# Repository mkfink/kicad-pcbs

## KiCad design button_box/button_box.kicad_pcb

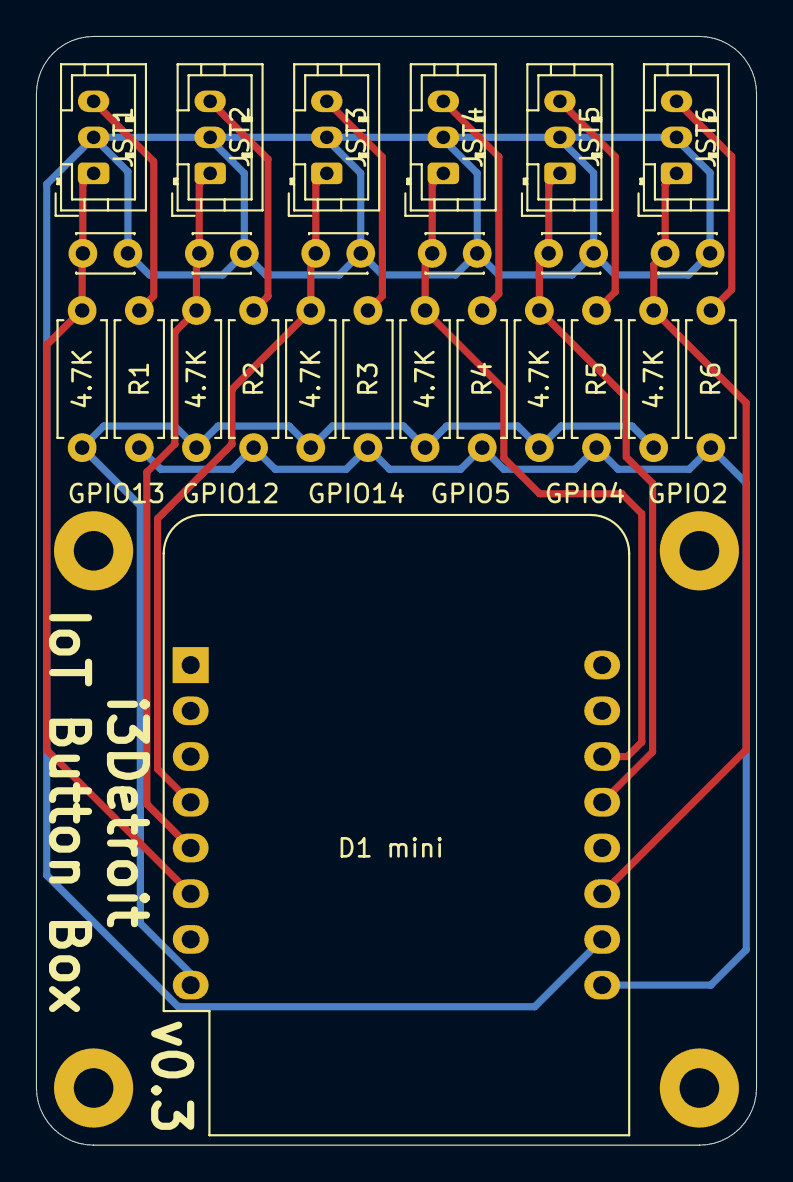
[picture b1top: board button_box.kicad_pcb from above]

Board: 2 copper layers, 40.0 x 61.6 mm, 29 parts (0 on the bottom side), 15 nets.

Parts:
4.7K, 4.7K#2, 4.7K#3, 4.7K#4, 4.7K#5, 4.7K#6: 4.7K; R_Axial_DIN0207_L6.3mm_D2.5mm_P7.62mm_Horizontal
C1, C2, C3, C4, C5, C6: 30 pF; C_Disc_D3.0mm_W2.0mm_P2.50mm
JST1, JST2, JST3, JST4, JST5, JST6: Conn_01x03_Male; JST_PH_B3B-PH-K_1x03_P2.00mm_Vertical
R1, R2, R3, R4, R5, R6: R; R_Axial_DIN0207_L6.3mm_D2.5mm_P7.62mm_Horizontal
U1: WeMos_D1_mini; WEMOS_D1_mini_light
hole: MountingHole_2.2mm_M2_Pad
hole#2, hole#3, hole#4: MountingHole_2.2mm_M2_Pad

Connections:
unnamed: 4.7K.1, C1.1, JST1.1, U1.6
unnamed: C1.2, C2.2, C3.2, C4.2, C5.2, C6.2, JST1.2, JST2.2, JST3.2, JST4.2, JST5.2, JST6.2, U1.10
unnamed: 4.7K#2.1, C2.1, JST2.1, U1.5
unnamed: 4.7K#3.1, C3.1, JST3.1, U1.4
unnamed: 4.7K#4.1, C4.1, JST4.1, U1.14
unnamed: 4.7K#5.1, C5.1, JST5.1, U1.13
unnamed: 4.7K#6.1, C6.1, JST6.1, U1.11
unnamed: JST6.3, R6.2
unnamed: JST5.3, R5.2
unnamed: JST4.3, R4.2
unnamed: JST3.3, R3.2
unnamed: JST2.3, R2.2
unnamed: JST1.3, R1.2
unnamed: R1.1, R2.1, R3.1, R4.1, R5.1, R6.1, U1.9
unnamed: 4.7K.2, 4.7K#2.2, 4.7K#3.2, 4.7K#4.2, 4.7K#5.2, 4.7K#6.2, U1.8

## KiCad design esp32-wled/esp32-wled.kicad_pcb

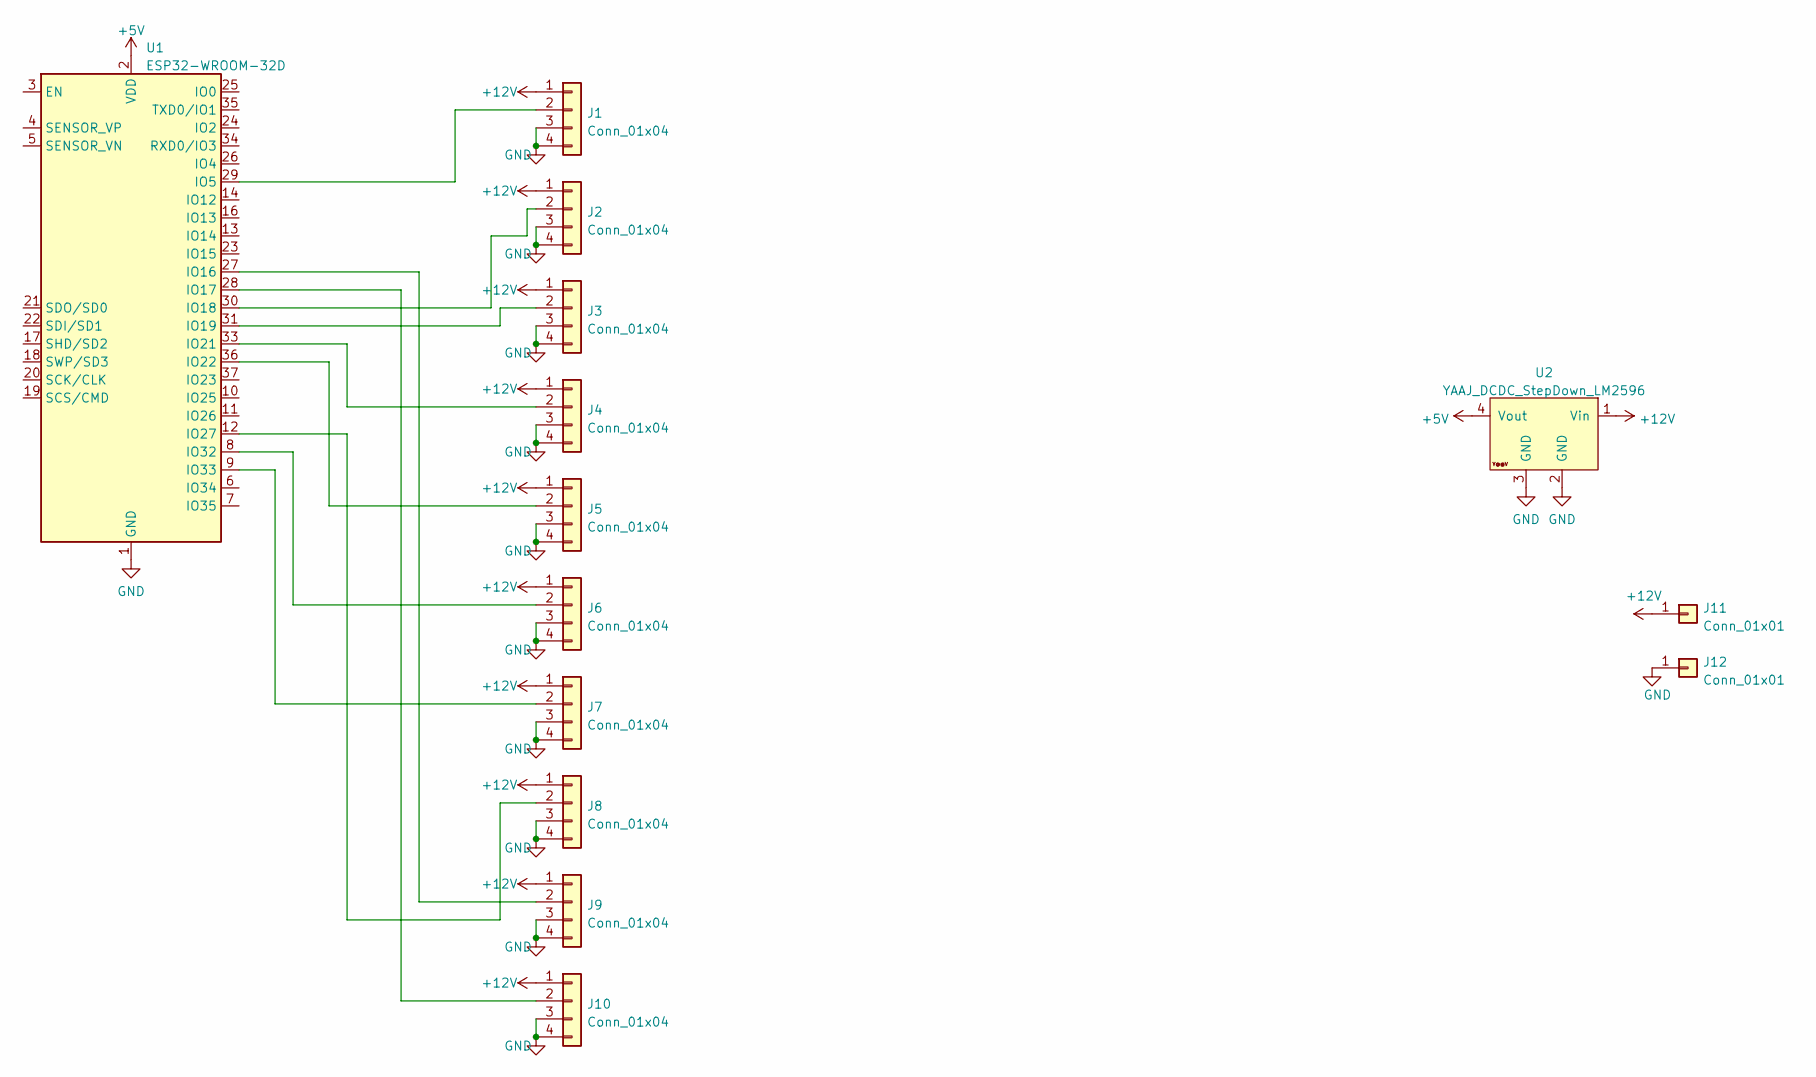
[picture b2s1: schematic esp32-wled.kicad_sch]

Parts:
J1, J2, J3, J4, J5, J6, J7, J8, J9, J10: Conn_01x04; JST_XH_S4B-XH-A_1x04_P2.50mm_Horizontal
J11, J12: Conn_01x01; Anderson_Powerpole-25A-RA-G1
U1: ESP32-WROOM-32D; ESP32-WROOM-32
U2: YAAJ_DCDC_StepDown_LM2596

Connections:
+5V: U1.2 (VDD), U2.4 (Vout)
+12V: J1.1, J2.1, J3.1, J4.1, J5.1, J6.1, J7.1, J8.1, J9.1, J10.1, J11.1, U2.1 (Vin)
GND: J1.3, J1.4, J2.3, J2.4, J3.3, J3.4, J4.3, J4.4, J5.3, J5.4, J6.3, J6.4, J7.3, J7.4, J8.3, J8.4, J9.3, J9.4, J10.3, J10.4, J12.1, U1.1 (GND), U1.15 (GND), U1.38 (GND), U1.39 (GND), U2.2 (GND), U2.3 (GND)
unnamed: J1.2, U1.29 (IO5)
unnamed: J2.2, U1.30 (IO18)
unnamed: J3.2, U1.31 (IO19)
unnamed: J4.2, U1.33 (IO21)
unnamed: J5.2, U1.36 (IO22)
unnamed: J6.2, U1.8 (IO32)
unnamed: J7.2, U1.9 (IO33)
unnamed: J8.2, U1.12 (IO27)
unnamed: J9.2, U1.27 (IO16)
unnamed: J10.2, U1.28 (IO17)

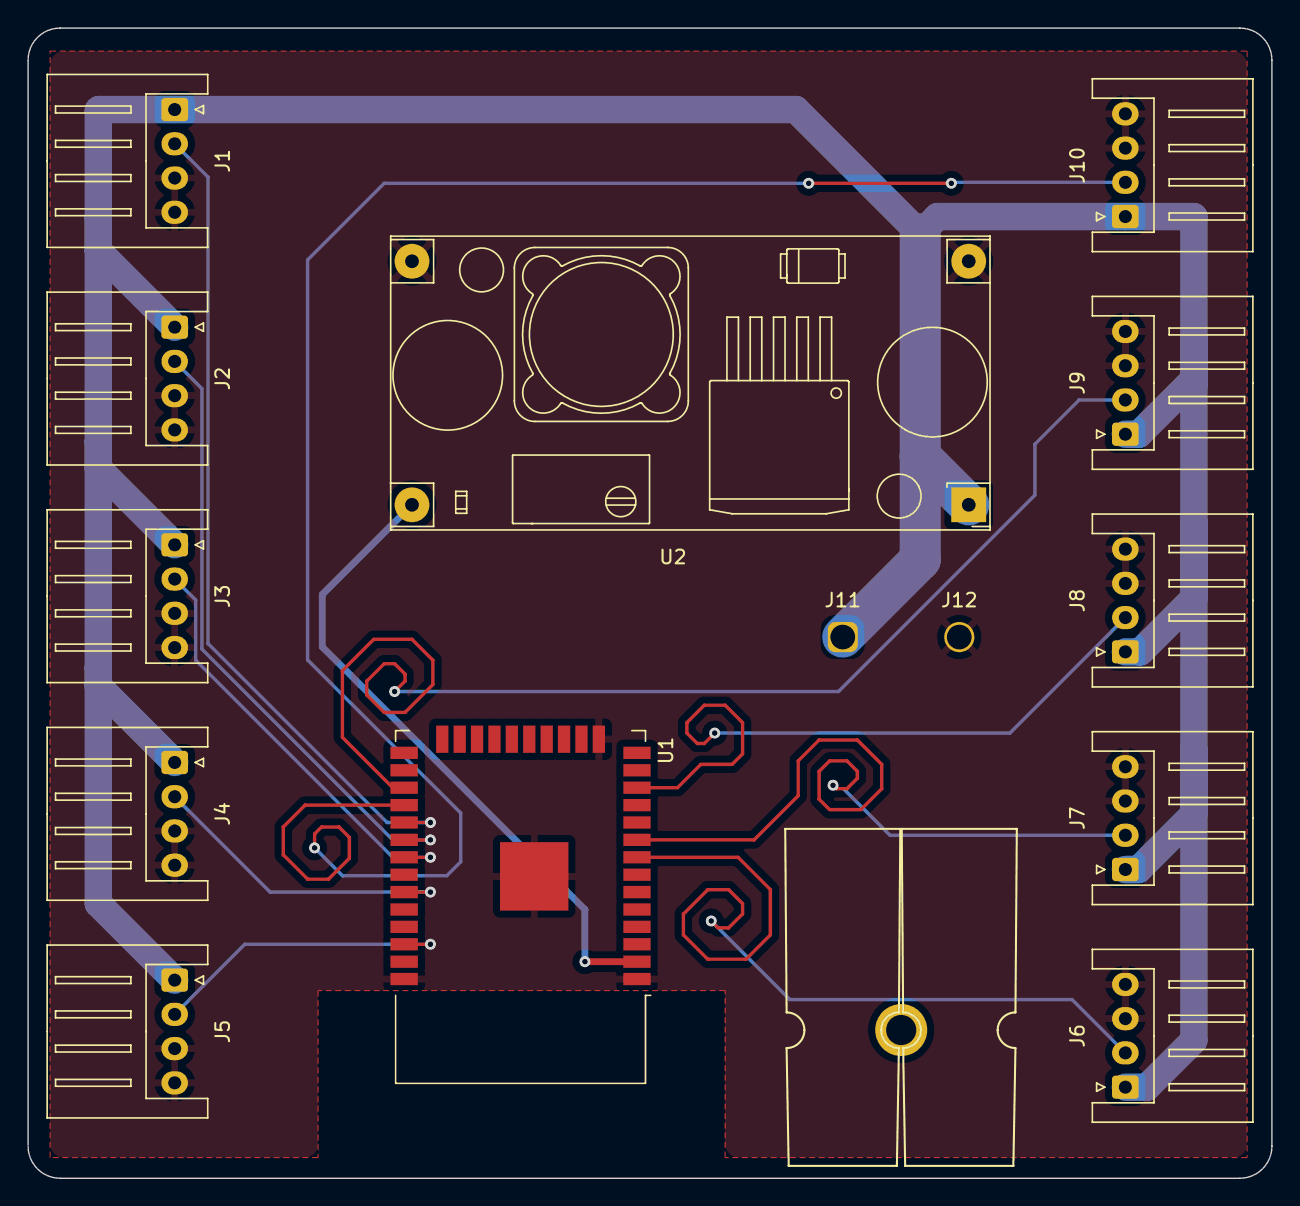
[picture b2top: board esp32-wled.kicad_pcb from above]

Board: 2 copper layers, 90.8 x 84.0 mm, 15 parts (0 on the bottom side), 13 nets.

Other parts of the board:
 : MountingHole_2.2mm_M2_DIN965_Pad

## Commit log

2022-08-21 add kicad gitignore
